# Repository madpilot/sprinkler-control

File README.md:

MC34063a calculator:

http://www.nomad.ee/micros/mc34063a/

Vin: 12V
Vout 3.3V
Iout: 750mA
Vripple: 100mv (pp)
Fmin: 30kHz

Ct=433 pF
Ipk=1500 mA
Rsc=0.2 Ohm
Lmin=56 uH
Co=63 uF
R1=11k R2=18k (3.3V)

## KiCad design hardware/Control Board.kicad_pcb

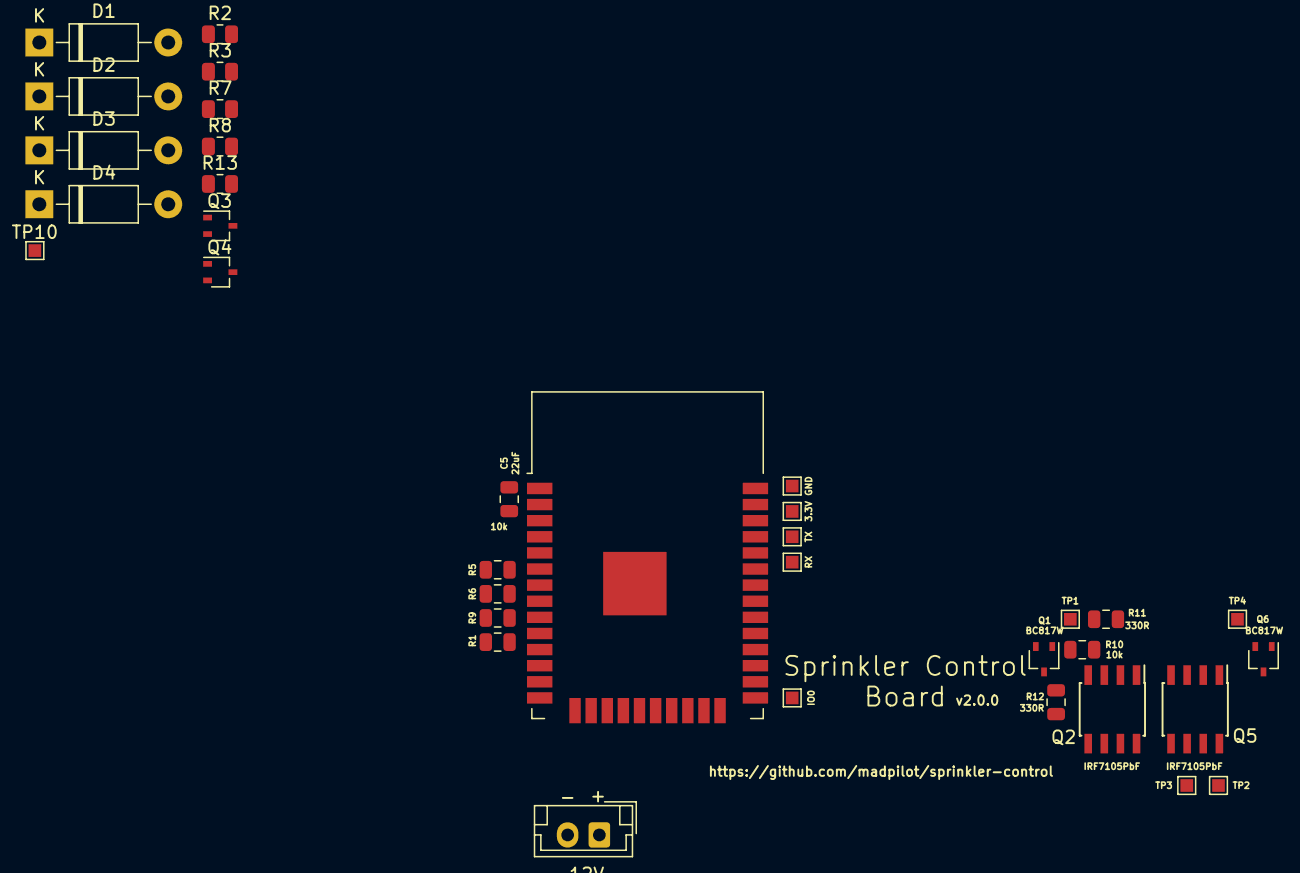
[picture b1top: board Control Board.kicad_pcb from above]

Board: 2 copper layers, 35 parts (0 on the bottom side), 24 nets, no tracks yet.

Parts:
C5: 22uF; C_0805_2012Metric
D1, D2, D3, D4: 1N4001; D_DO-41_SOD81_P10.16mm_Horizontal
J1: 12V; JST_EH_B02B-EH-A_1x02_P2.50mm_Vertical
Q1, Q3, Q4, Q6: BC817W; SOT-323_SC-70
Q2, Q5: IRF7105PbF; SOIC-8_3.9x4.9mm_P1.27mm
R1, R3, R5, R6, R7, R9, R10, R13: 10k; R_0805_2012Metric
R2, R8, R11, R12: 330R; R_0805_2012Metric
TP1, TP2, TP3, TP4, TP10: TestPoint; TestPoint_Pad_1.0x1.0mm
TP5: 3.3V; TestPoint_Pad_1.0x1.0mm
TP6: RX; TestPoint_Pad_1.0x1.0mm
TP7: TX; TestPoint_Pad_1.0x1.0mm
TP8: IO0; TestPoint_Pad_1.0x1.0mm
TP9: GND; TestPoint_Pad_1.0x1.0mm
U2: ESP32-WROVER; ESP32-WROOM-32

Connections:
+3V3: C5.1, R1.1, R5.1, R6.1, R9.1, TP5.1, U2.2 (3V3)
+12V: D1.1 (K), D4.1 (K), J1.1, Q2.7 (D1), Q2.8 (D1), Q5.7 (D1), Q5.8 (D1), R2.1, R8.1, R11.1, R12.1
CHANNEL_1: R10.2, TP1.1, U2.31 (IO19)
CHANNEL_2: R3.1, TP2.1, U2.30 (IO18)
CHANNEL_3: R7.2, TP3.1, U2.33 (IO21)
CHANNEL_4: R13.1, TP4.1, U2.36 (IO22)
GND: C5.2, D2.2 (A), D3.2 (A), J1.2, Q1.2 (E), Q2.3 (S2), Q3.2 (E), Q4.2 (E), Q5.3 (S2), Q6.2 (E), TP9.1, TP10.1, U2.1 (GND), U2.15 (GND), U2.38 (GND), U2.39 (GND)
IO0: TP8.1, U2.25 (IO0)
unnamed: D1.2 (A), Q2.4 (G2), Q3.3 (C), R2.2
unnamed: D2.1 (K), Q1.3 (C), Q2.2 (G1), R12.2
unnamed: D3.1 (K), Q4.3 (C), Q5.2 (G1), R8.2
unnamed: D4.2 (A), Q5.4 (G2), Q6.3 (C), R11.2
unnamed: Q2.5 (D2), Q2.6 (D2)
unnamed: Q5.5 (D2), Q5.6 (D2)
unnamed: Q1.1 (B), R10.1
unnamed: Q3.1 (B), R3.2
unnamed: Q4.1 (B), R7.1
unnamed: Q6.1 (B), R13.2
unnamed: R6.2, U2.8 (IO32_XTAL_32K_P)
unnamed: R9.2, U2.9 (IO33_XTAL_32K_N)
unnamed: R1.2, U2.6 (IO34)
unnamed: R5.2, U2.7 (IO35)
RX: TP6.1, U2.34 (RXD0)
TX: TP7.1, U2.35 (TXD0)

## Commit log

2021-04-06 Checking in version 1.0.0
2021-04-06 Add pull up resistors on the auto programmer circuit, switch the RX and TX lines
2021-04-06 Placing the pull ups on the programmer
2021-04-06 Fixing silkscreen on pull ups
2021-04-06 RX and TX were crossing over, adding spots for capacitors on EN and IO0
2021-04-06 adding a skeleton firmware
2021-04-06 Broke the pcb during a merge.
2021-04-07 Using 5V FTDI, adding protection diodes to allow dual power, adding some additional bypass caps
2021-04-07 Cleaning up some silk screens
2021-05-06 Wiring up new layout
2021-05-06 Copying board from firmware/powered
2021-05-12 Routing MOSFETs
2021-05-20 Adding mounting holes
2021-05-20 Moving + and - solar pads away from the screw head
2021-05-20 Moving batt via away from the screw head
2021-05-20 Moving Q2 and Q5 identifiers
2021-10-08 Move to 12V, use power supply module, remove auto programmer, remove solar charger, Use ESP32-WROVER
2021-10-28 Version 2.0
2024-09-08 Fixing MOSFETs, moving over to using a buck converter
2024-09-08 Updating values of PSU
